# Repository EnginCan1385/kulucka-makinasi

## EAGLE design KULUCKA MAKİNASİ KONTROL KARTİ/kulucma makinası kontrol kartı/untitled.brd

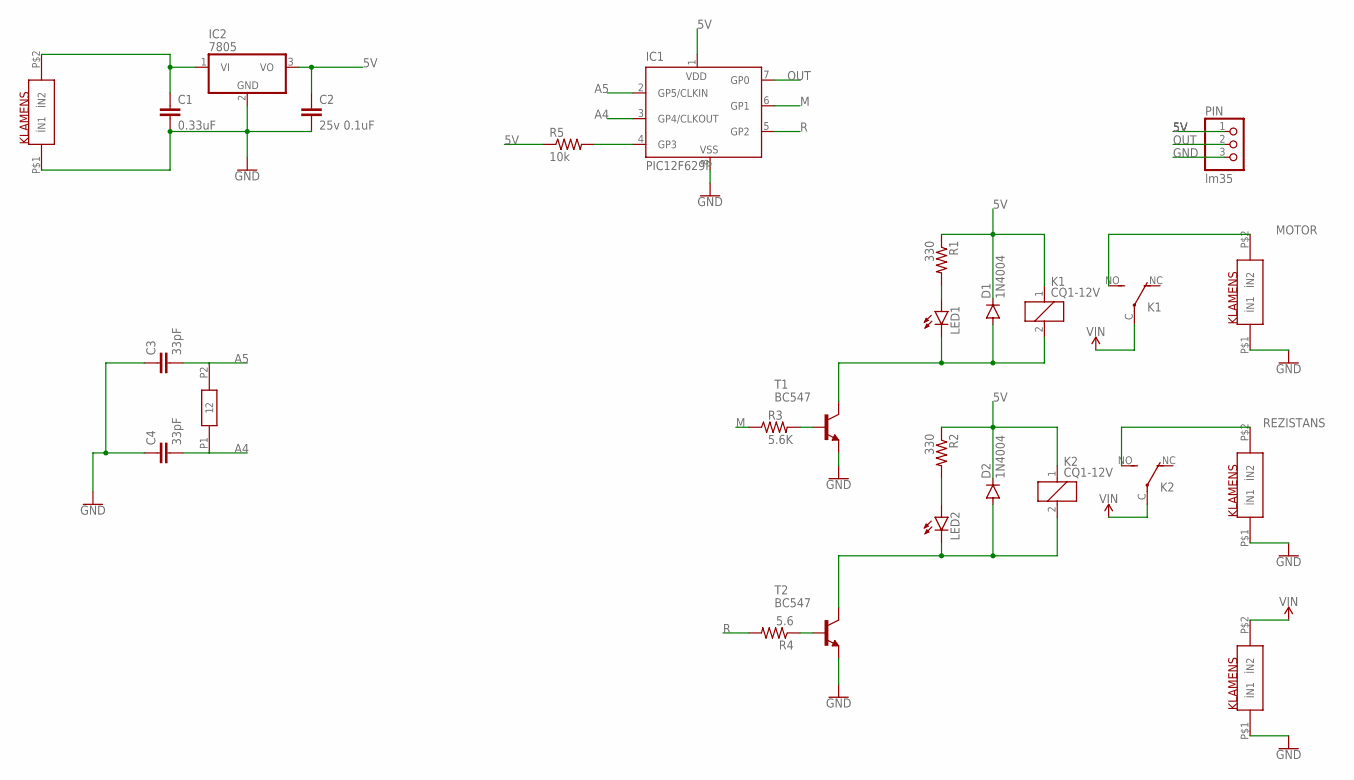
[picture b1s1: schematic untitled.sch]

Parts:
C1: 0.33uF; C2.5-6
C2: 25v 0.1uF; C2.5-6
C3, C4: 33pF; C2.5-6
D1, D2: 1N4004; DO41-10
IC1: PIC12F629P; DIL8
IC2: 7805; TO220H
K1, K2: CQ1-12V; CQ1
LED1, LED2: LED3MM
PIN: lm35; 1X03
R1, R2: 330; 0207/10
R3: 5.6K; 0207/10
R4: 5.6; 0207/10
R5: 10k; 0207/10
T1, T2: BC547; TO92
U$1, U$2, U$3, U$5: KLAMENS
U$6: KIRISTAL

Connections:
5V: C2.1, D1.C, D2.C, IC1.1 (VDD), IC2.3 (VO), K1.1, K2.1, PIN.1, R1.1, R2.1, R5.1
A4: C4.2, IC1.3 (GP4/CLKOUT), U$6.P1 (1)
A5: C3.2, IC1.2 (GP5/CLKIN), U$6.P2 (2)
GND: C1.2, C2.2, C3.1, C4.1, IC1.8 (VSS), IC2.2 (GND), PIN.3, T1.1 (E), T2.1 (E), U$1.P$1 (İN1), U$2.P$1 (İN1), U$3.P$1 (İN1), U$5.P$1 (İN1)
M: IC1.6 (GP1), R3.1
MOTOR: K1.NO (S), U$1.P$2 (İN2)
unnamed: R3.2, T1.2 (B)
unnamed: LED2.A, R2.2
unnamed: D2.A, K2.2, LED2.K (C), T2.3 (C)
unnamed: R4.1, T2.2 (B)
unnamed: LED1.A, R1.2
unnamed: D1.A, K1.2, LED1.K (C), T1.3 (C)
unnamed: C1.1, IC2.1 (VI), U$5.P$2 (İN2)
unnamed: IC1.4 (GP3), R5.2
OUT: IC1.7 (GP0), PIN.2
R: IC1.5 (GP2), R4.2
REZISTANS: K2.NO (S), U$2.P$2 (İN2)
VIN: K1.C, K2.C, U$3.P$2 (İN2)

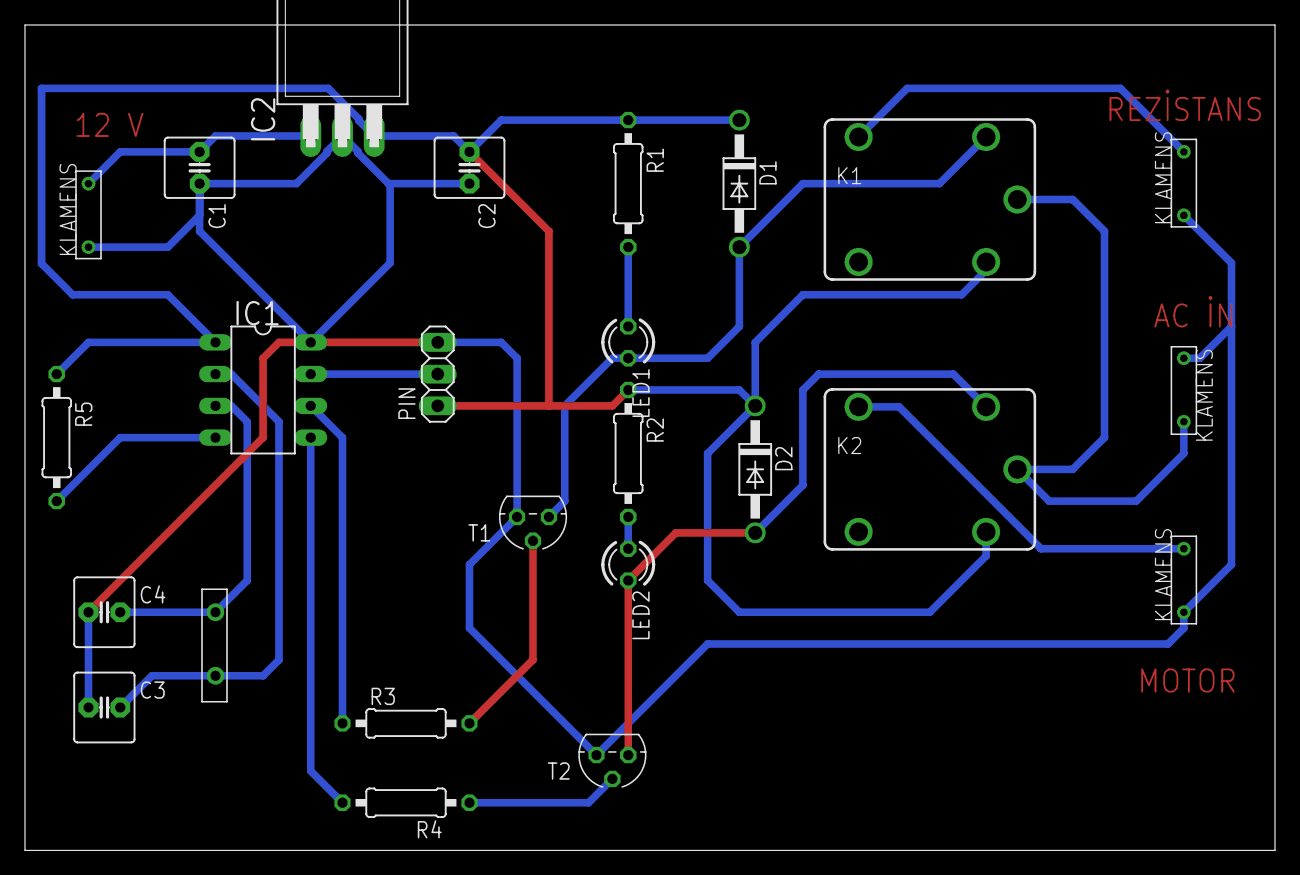
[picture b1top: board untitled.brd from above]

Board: 2 copper layers, 100.0 x 66.0 mm, 25 parts (0 on the bottom side), 18 nets.

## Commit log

2022-04-09 pic12f675 ile kuluçka makinasi yapımı
    Projemizde pic12f675 kullanılmıştır.AN0 bacağından 10 bitlik analog okuma yapılıyor,okunan deger kodlarda görüldüğü üzere önce gerilime daha sonrada sıcaklığa çeviriliyor.37 derecen düşükse ısıtıcı d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

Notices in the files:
parts and their libraries:
SparkFun-PowerSymbols: Licensing: Creative Commons ShareAlike 4.0 International - https://creativecommons.org/licenses/by-sa/4.0
